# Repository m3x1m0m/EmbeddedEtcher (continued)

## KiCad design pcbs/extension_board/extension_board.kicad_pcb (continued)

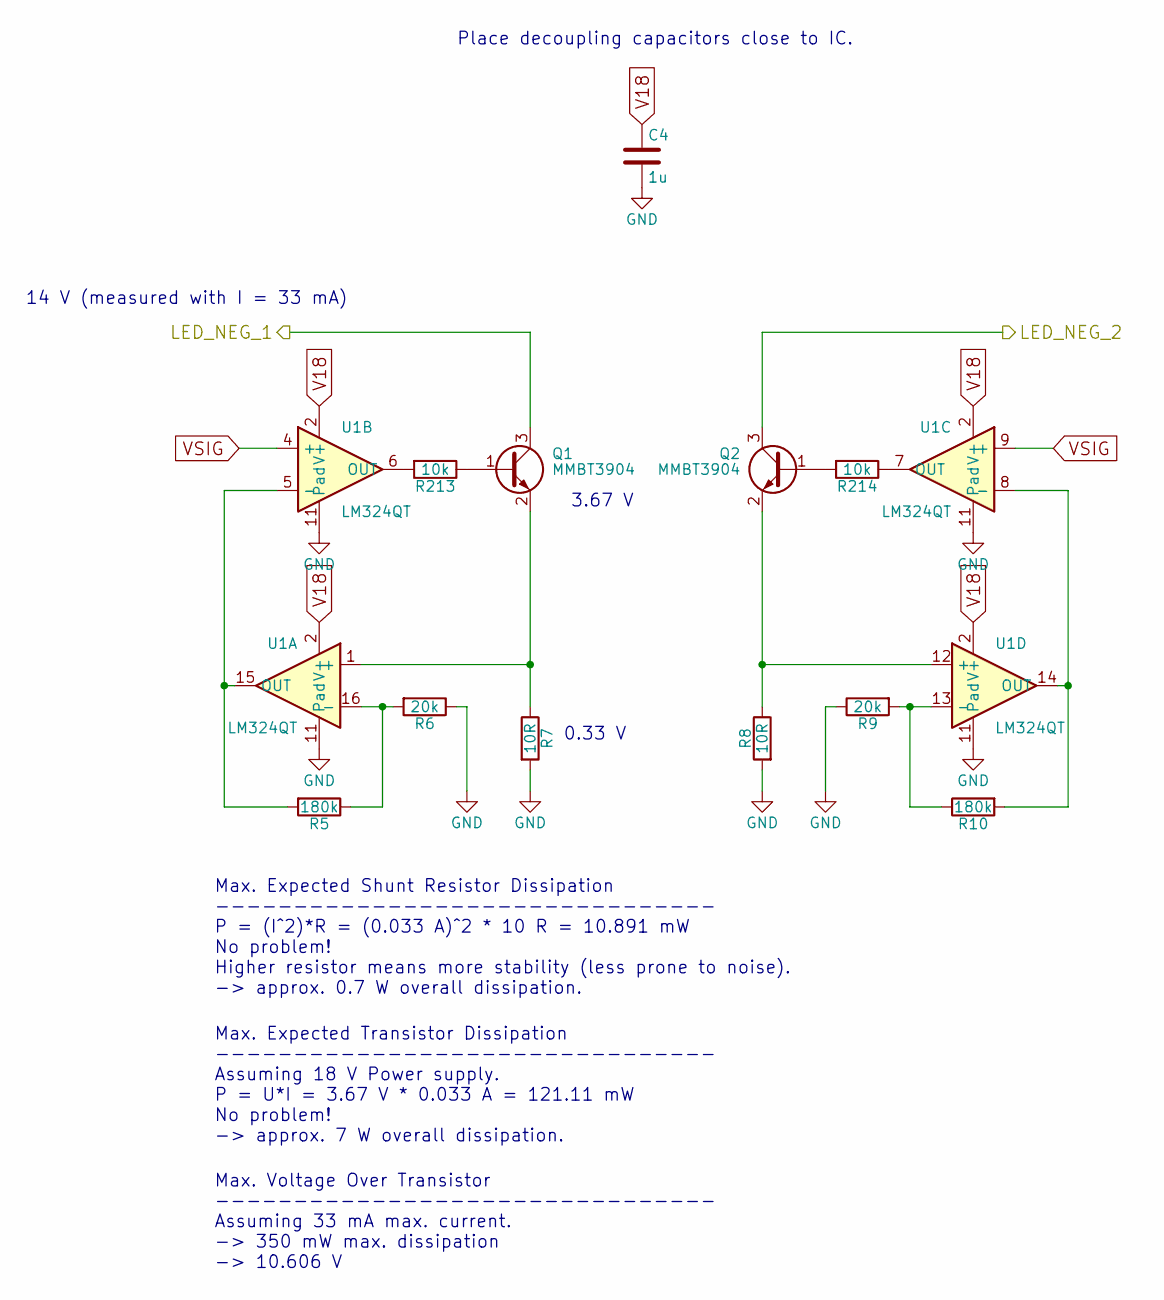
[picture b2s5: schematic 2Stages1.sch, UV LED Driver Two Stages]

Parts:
C4: 1u; R_0603; Digikey 399-3118-1-ND
Q1, Q2: MMBT3904; SOT-23; Digikey MMBT3904TPMSCT-ND
R5, R10: 180k; R_0603; Digikey 311-180KHRCT-ND
R6, R9: 20k; R_0603; Digikey 311-20.0KHRCT-ND
R7, R8: 10R; R_0603; Digikey 311-10.0HRCT-ND
R213, R214: 10k; R_0603; Digikey 311-10KGRCT-ND
U1: LM324QT; QFN-16-1EP_3x3mm_Pitch0.5mm; Digikey 497-12005-1-ND

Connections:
GND: C4.2, R6.1, R7.2, R8.2, R9.1, U1.11 (Pad), U1.17 (Pad); also elsewhere on the board
LED_N_01: Q1.3 (C); also elsewhere on the board
LED_N_02: Q2.3 (C); also elsewhere on the board
unnamed: Q1.1 (B), R213.1
unnamed: Q1.2 (E), R7.1, U1.1 (+)
unnamed: Q2.1 (B), R214.2
unnamed: Q2.2 (E), R8.1, U1.12 (+)
unnamed: R5.1, R6.2, U1.16 (-)
unnamed: R5.2, U1.5 (-), U1.15 (OUT)
unnamed: R9.2, R10.1, U1.13 (-)
unnamed: R10.2, U1.8 (-), U1.14 (OUT)
unnamed: R213.2, U1.6 (OUT)
unnamed: R214.1, U1.7 (OUT)
V18: C4.1, U1.2 (V+); also elsewhere on the board
VSIG: U1.4 (+), U1.9 (+); also elsewhere on the board

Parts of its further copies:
C8, C12, C16, C20, C24, C28, C32, C36, C40, C44, C48, C52, C56, C60, C64, C68, C72, C76, C80, C84, C88, C92, C96, C100, C104, C108, C112, C116, C120, C124, C128: 1u; R_0603; Digikey 399-3118-1-ND
Q3, Q4, Q5, Q6, Q7, Q8, Q9, Q10, Q11, Q12, Q13, Q14, Q15, Q16, Q17, Q18, Q19, Q20, Q21, Q22, Q23, Q24, Q25, Q26, Q27, Q28, Q29, Q30, Q31, Q32, Q33, Q34, Q35, Q36, Q37, Q38, Q39, Q40, Q41, Q42, Q43, Q44, Q45, Q46, Q47, Q48, Q49, Q50, Q51, Q52, Q53, Q54, Q55, Q56, Q57, Q58, Q59, Q60, Q61, Q62, Q63, Q64: MMBT3904; SOT-23; Digikey MMBT3904TPMSCT-ND
R11, R16, R17, R22, R23, R28, R29, R34, R35, R40, R41, R46, R47, R52, R53, R58, R59, R64, R65, R70, R71, R76, R77, R82, R83, R88, R89, R94, R95, R100, R101, R106, R107, R112, R113, R118, R119, R124, R125, R130, R131, R136, R137, R142, R143, R148, R149, R154, R155, R160, R161, R166, R167, R172, R173, R178, R179, R184, R185, R190, R191, R196: 180k; R_0603; Digikey 311-180KHRCT-ND
R12, R15, R18, R21, R24, R27, R30, R33, R36, R39, R42, R45, R48, R51, R54, R57, R60, R63, R66, R69, R72, R75, R78, R81, R84, R87, R90, R93, R96, R99, R102, R105, R108, R111, R114, R117, R120, R123, R126, R129, R132, R135, R138, R141, R144, R147, R150, R153, R156, R159, R162, R165, R168, R171, R174, R177, R180, R183, R186, R189, R192, R195: 20k; R_0603; Digikey 311-20.0KHRCT-ND
R13, R14, R19, R20, R25, R26, R31, R32, R37, R38, R43, R44, R49, R50, R55, R56, R61, R62, R67, R68, R73, R74, R79, R80, R85, R86, R91, R92, R97, R98, R103, R104, R109, R110, R115, R116, R121, R122, R127, R128, R133, R134, R139, R140, R145, R146, R151, R152, R157, R158, R163, R164, R169, R170, R175, R176, R181, R182, R187, R188, R193, R194: 10R; R_0603; Digikey 311-10.0HRCT-ND
R215, R216, R217, R218, R219, R220, R221, R222, R223, R224, R225, R226, R227, R228, R229, R230, R231, R232, R233, R234, R235, R236, R237, R238, R239, R240, R241, R242, R243, R244, R245, R246, R247, R248, R249, R250, R251, R252, R253, R254, R255, R256, R257, R258, R259, R260, R261, R262, R263, R264, R265, R266, R267, R268, R269, R270, R271, R272, R273, R274, R275, R276: 10k; R_0603; Digikey 311-10KGRCT-ND
U2, U3, U4, U5, U6, U7, U8, U9, U10, U11, U12, U13, U14, U15, U16, U17, U18, U19, U20, U21, U22, U23, U24, U25, U26, U27, U28, U29, U30, U31, U32: LM324QT; QFN-16-1EP_3x3mm_Pitch0.5mm; Digikey 497-12005-1-ND

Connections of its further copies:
GND: C8.2, C12.2, C16.2, C20.2, C24.2, C28.2, C32.2, C36.2, C40.2, C44.2, C48.2, C52.2, C56.2, C60.2, C64.2, C68.2, C72.2, C76.2, C80.2, C84.2, C88.2, C92.2, C96.2, C100.2, C104.2, C108.2, C112.2, C116.2, C120.2, C124.2, C128.2, R12.1, R13.2, R14.2, R15.1, R18.1, R19.2, R20.2, R21.1, R24.1, R25.2, R26.2, R27.1, R30.1, R31.2, R32.2, R33.1, R36.1, R37.2, R38.2, R39.1, R42.1, R43.2, R44.2, R45.1, R48.1, R49.2, R50.2, R51.1, R54.1, R55.2, R56.2, R57.1, R60.1, R61.2, R62.2, R63.1, R66.1, R67.2, R68.2, R69.1, R72.1, R73.2, R74.2, R75.1, R78.1, R79.2, R80.2, R81.1, R84.1, R85.2, R86.2, R87.1, R90.1, R91.2, R92.2, R93.1, R96.1, R97.2, R98.2, R99.1, R102.1, R103.2, R104.2, R105.1, R108.1, R109.2, R110.2, R111.1, R114.1, R115.2, R116.2, R117.1, R120.1, R121.2, R122.2, R123.1, R126.1, R127.2, R128.2, R129.1, R132.1, R133.2, R134.2, R135.1, R138.1, R139.2, R140.2, R141.1, R144.1, R145.2, R146.2, R147.1, R150.1, R151.2, R152.2, R153.1, R156.1, R157.2, R158.2, R159.1, R162.1, R163.2, R164.2, R165.1, R168.1, R169.2, R170.2, R171.1, R174.1, R175.2, R176.2, R177.1, R180.1, R181.2, R182.2, R183.1, R186.1, R187.2, R188.2, R189.1, R192.1, R193.2, R194.2, R195.1, U2.11 (Pad), U2.17 (Pad), U3.11 (Pad), U3.17 (Pad), U4.11 (Pad), U4.17 (Pad), U5.11 (Pad), U5.17 (Pad), U6.11 (Pad), U6.17 (Pad), U7.11 (Pad), U7.17 (Pad), U8.11 (Pad), U8.17 (Pad), U9.11 (Pad), U9.17 (Pad), U10.11 (Pad), U10.17 (Pad), U11.11 (Pad), U11.17 (Pad), U12.11 (Pad), U12.17 (Pad), U13.11 (Pad), U13.17 (Pad), U14.11 (Pad), U14.17 (Pad), U15.11 (Pad), U15.17 (Pad), U16.11 (Pad), U16.17 (Pad), U17.11 (Pad), U17.17 (Pad), U18.11 (Pad), U18.17 (Pad), U19.11 (Pad), U19.17 (Pad), U20.11 (Pad), U20.17 (Pad), U21.11 (Pad), U21.17 (Pad), U22.11 (Pad), U22.17 (Pad), U23.11 (Pad), U23.17 (Pad), U24.11 (Pad), U24.17 (Pad), U25.11 (Pad), U25.17 (Pad), U26.11 (Pad), U26.17 (Pad), U27.11 (Pad), U27.17 (Pad), U28.11 (Pad), U28.17 (Pad), U29.11 (Pad), U29.17 (Pad), U30.11 (Pad), U30.17 (Pad), U31.11 (Pad), U31.17 (Pad), U32.11 (Pad), U32.17 (Pad); also elsewhere on the board
LED_N_03: Q3.3 (C); also elsewhere on the board
LED_N_04: Q4.3 (C); also elsewhere on the board
LED_N_05: Q5.3 (C); also elsewhere on the board
LED_N_06: Q6.3 (C); also elsewhere on the board
LED_N_07: Q7.3 (C); also elsewhere on the board
LED_N_08: Q8.3 (C); also elsewhere on the board
LED_N_09: Q9.3 (C); also elsewhere on the board
LED_N_10: Q10.3 (C); also elsewhere on the board
LED_N_11: Q11.3 (C); also elsewhere on the board
LED_N_12: Q12.3 (C); also elsewhere on the board
LED_N_13: Q13.3 (C); also elsewhere on the board
LED_N_14: Q14.3 (C); also elsewhere on the board
LED_N_15: Q15.3 (C); also elsewhere on the board
LED_N_16: Q16.3 (C); also elsewhere on the board
LED_N_17: Q17.3 (C); also elsewhere on the board
LED_N_18: Q18.3 (C); also elsewhere on the board
LED_N_19: Q19.3 (C); also elsewhere on the board
LED_N_20: Q20.3 (C); also elsewhere on the board
LED_N_21: Q21.3 (C); also elsewhere on the board
LED_N_22: Q22.3 (C); also elsewhere on the board
LED_N_23: Q23.3 (C); also elsewhere on the board
LED_N_24: Q24.3 (C); also elsewhere on the board
LED_N_25: Q25.3 (C); also elsewhere on the board
LED_N_26: Q26.3 (C); also elsewhere on the board
LED_N_27: Q27.3 (C); also elsewhere on the board
LED_N_28: Q28.3 (C); also elsewhere on the board
LED_N_29: Q29.3 (C); also elsewhere on the board
LED_N_30: Q30.3 (C); also elsewhere on the board
LED_N_31: Q31.3 (C); also elsewhere on the board
LED_N_32: Q32.3 (C); also elsewhere on the board
LED_N_33: Q34.3 (C); also elsewhere on the board
LED_N_34: Q33.3 (C); also elsewhere on the board
LED_N_35: Q36.3 (C); also elsewhere on the board
LED_N_36: Q35.3 (C); also elsewhere on the board
LED_N_37: Q38.3 (C); also elsewhere on the board
LED_N_38: Q37.3 (C); also elsewhere on the board
LED_N_39: Q40.3 (C); also elsewhere on the board
LED_N_40: Q39.3 (C); also elsewhere on the board
LED_N_41: Q42.3 (C); also elsewhere on the board
LED_N_42: Q41.3 (C); also elsewhere on the board
LED_N_43: Q44.3 (C); also elsewhere on the board
LED_N_44: Q43.3 (C); also elsewhere on the board
LED_N_45: Q46.3 (C); also elsewhere on the board
LED_N_46: Q45.3 (C); also elsewhere on the board
LED_N_47: Q48.3 (C); also elsewhere on the board
LED_N_48: Q47.3 (C); also elsewhere on the board
LED_N_49: Q50.3 (C); also elsewhere on the board
LED_N_50: Q49.3 (C); also elsewhere on the board
LED_N_51: Q52.3 (C); also elsewhere on the board
LED_N_52: Q51.3 (C); also elsewhere on the board
LED_N_53: Q54.3 (C); also elsewhere on the board
LED_N_54: Q53.3 (C); also elsewhere on the board
LED_N_55: Q56.3 (C); also elsewhere on the board
LED_N_56: Q55.3 (C); also elsewhere on the board
LED_N_57: Q58.3 (C); also elsewhere on the board
LED_N_58: Q57.3 (C); also elsewhere on the board
LED_N_59: Q60.3 (C); also elsewhere on the board
LED_N_60: Q59.3 (C); also elsewhere on the board
LED_N_61: Q62.3 (C); also elsewhere on the board
LED_N_62: Q61.3 (C); also elsewhere on the board
LED_N_63: Q64.3 (C); also elsewhere on the board
LED_N_64: Q63.3 (C); also elsewhere on the board
unnamed: Q3.1 (B), R215.1
unnamed: Q3.2 (E), R13.1, U2.1 (+)
unnamed: Q4.1 (B), R216.2
unnamed: Q4.2 (E), R14.1, U2.12 (+)
unnamed: Q5.1 (B), R217.1
unnamed: Q5.2 (E), R19.1, U3.1 (+)
unnamed: Q6.1 (B), R218.2
unnamed: Q6.2 (E), R20.1, U3.12 (+)
unnamed: Q7.1 (B), R219.1
unnamed: Q7.2 (E), R25.1, U4.1 (+)
unnamed: Q8.1 (B), R220.2
unnamed: Q8.2 (E), R26.1, U4.12 (+)
unnamed: Q9.1 (B), R221.1
unnamed: Q9.2 (E), R31.1, U5.1 (+)
unnamed: Q10.1 (B), R222.2
unnamed: Q10.2 (E), R32.1, U5.12 (+)
unnamed: Q11.1 (B), R223.1
unnamed: Q11.2 (E), R37.1, U6.1 (+)
unnamed: Q12.1 (B), R224.2
unnamed: Q12.2 (E), R38.1, U6.12 (+)
unnamed: Q13.1 (B), R225.1
unnamed: Q13.2 (E), R43.1, U7.1 (+)
unnamed: Q14.1 (B), R226.2
unnamed: Q14.2 (E), R44.1, U7.12 (+)
unnamed: Q15.1 (B), R227.1
unnamed: Q15.2 (E), R49.1, U8.1 (+)
unnamed: Q16.1 (B), R228.2
unnamed: Q16.2 (E), R50.1, U8.12 (+)
unnamed: Q17.1 (B), R229.1
unnamed: Q17.2 (E), R55.1, U9.1 (+)
unnamed: Q18.1 (B), R230.2
unnamed: Q18.2 (E), R56.1, U9.12 (+)
unnamed: Q19.1 (B), R231.1
unnamed: Q19.2 (E), R61.1, U10.1 (+)
unnamed: Q20.1 (B), R232.2
unnamed: Q20.2 (E), R62.1, U10.12 (+)
unnamed: Q21.1 (B), R233.1
unnamed: Q21.2 (E), R67.1, U11.1 (+)
unnamed: Q22.1 (B), R234.2
unnamed: Q22.2 (E), R68.1, U11.12 (+)
unnamed: Q23.1 (B), R235.1
unnamed: Q23.2 (E), R73.1, U12.1 (+)
unnamed: Q24.1 (B), R236.2
unnamed: Q24.2 (E), R74.1, U12.12 (+)
unnamed: Q25.1 (B), R237.1
unnamed: Q25.2 (E), R79.1, U13.1 (+)
unnamed: Q26.1 (B), R238.2
unnamed: Q26.2 (E), R80.1, U13.12 (+)
unnamed: Q27.1 (B), R239.1
unnamed: Q27.2 (E), R85.1, U14.1 (+)
unnamed: Q28.1 (B), R240.2
unnamed: Q28.2 (E), R86.1, U14.12 (+)
unnamed: Q29.1 (B), R241.1
unnamed: Q29.2 (E), R91.1, U15.1 (+)
unnamed: Q30.1 (B), R242.2
unnamed: Q30.2 (E), R92.1, U15.12 (+)
unnamed: Q31.1 (B), R243.1
unnamed: Q31.2 (E), R97.1, U16.1 (+)
unnamed: Q32.1 (B), R244.2
unnamed: Q32.2 (E), R98.1, U16.12 (+)
unnamed: Q33.1 (B), R275.1
unnamed: Q33.2 (E), R193.1, U17.1 (+)
unnamed: Q34.1 (B), R276.2
unnamed: Q34.2 (E), R194.1, U17.12 (+)
unnamed: Q35.1 (B), R273.1
unnamed: Q35.2 (E), R187.1, U18.1 (+)
unnamed: Q36.1 (B), R274.2
unnamed: Q36.2 (E), R188.1, U18.12 (+)
unnamed: Q37.1 (B), R271.1
unnamed: Q37.2 (E), R181.1, U19.1 (+)
unnamed: Q38.1 (B), R272.2
unnamed: Q38.2 (E), R182.1, U19.12 (+)
unnamed: Q39.1 (B), R269.1
unnamed: Q39.2 (E), R175.1, U20.1 (+)
unnamed: Q40.1 (B), R270.2
unnamed: Q40.2 (E), R176.1, U20.12 (+)
unnamed: Q41.1 (B), R267.1
unnamed: Q41.2 (E), R169.1, U21.1 (+)
unnamed: Q42.1 (B), R268.2
unnamed: Q42.2 (E), R170.1, U21.12 (+)
unnamed: Q43.1 (B), R265.1
unnamed: Q43.2 (E), R163.1, U22.1 (+)
unnamed: Q44.1 (B), R266.2
unnamed: Q44.2 (E), R164.1, U22.12 (+)
unnamed: Q45.1 (B), R263.1
unnamed: Q45.2 (E), R157.1, U23.1 (+)
unnamed: Q46.1 (B), R264.2
unnamed: Q46.2 (E), R158.1, U23.12 (+)
unnamed: Q47.1 (B), R261.1
unnamed: Q47.2 (E), R151.1, U24.1 (+)
unnamed: Q48.1 (B), R262.2
unnamed: Q48.2 (E), R152.1, U24.12 (+)
unnamed: Q49.1 (B), R259.1
unnamed: Q49.2 (E), R145.1, U25.1 (+)
unnamed: Q50.1 (B), R260.2
unnamed: Q50.2 (E), R146.1, U25.12 (+)
unnamed: Q51.1 (B), R257.1
unnamed: Q51.2 (E), R139.1, U26.1 (+)
unnamed: Q52.1 (B), R258.2
unnamed: Q52.2 (E), R140.1, U26.12 (+)
unnamed: Q53.1 (B), R255.1
unnamed: Q53.2 (E), R133.1, U27.1 (+)
unnamed: Q54.1 (B), R256.2
unnamed: Q54.2 (E), R134.1, U27.12 (+)
unnamed: Q55.1 (B), R253.1
unnamed: Q55.2 (E), R127.1, U28.1 (+)
unnamed: Q56.1 (B), R254.2
unnamed: Q56.2 (E), R128.1, U28.12 (+)
unnamed: Q57.1 (B), R251.1
unnamed: Q57.2 (E), R121.1, U29.1 (+)
unnamed: Q58.1 (B), R252.2
unnamed: Q58.2 (E), R122.1, U29.12 (+)
unnamed: Q59.1 (B), R249.1
unnamed: Q59.2 (E), R115.1, U30.1 (+)
unnamed: Q60.1 (B), R250.2
unnamed: Q60.2 (E), R116.1, U30.12 (+)
unnamed: Q61.1 (B), R247.1
unnamed: Q61.2 (E), R109.1, U31.1 (+)
unnamed: Q62.1 (B), R248.2
unnamed: Q62.2 (E), R110.1, U31.12 (+)
unnamed: Q63.1 (B), R245.1
unnamed: Q63.2 (E), R103.1, U32.1 (+)
unnamed: Q64.1 (B), R246.2
unnamed: Q64.2 (E), R104.1, U32.12 (+)
unnamed: R11.1, R12.2, U2.16 (-)
unnamed: R11.2, U2.5 (-), U2.15 (OUT)
unnamed: R15.2, R16.1, U2.13 (-)
unnamed: R16.2, U2.8 (-), U2.14 (OUT)
unnamed: R17.1, R18.2, U3.16 (-)
unnamed: R17.2, U3.5 (-), U3.15 (OUT)
unnamed: R21.2, R22.1, U3.13 (-)
unnamed: R22.2, U3.8 (-), U3.14 (OUT)
unnamed: R23.1, R24.2, U4.16 (-)
unnamed: R23.2, U4.5 (-), U4.15 (OUT)
unnamed: R27.2, R28.1, U4.13 (-)
unnamed: R28.2, U4.8 (-), U4.14 (OUT)
unnamed: R29.1, R30.2, U5.16 (-)
unnamed: R29.2, U5.5 (-), U5.15 (OUT)
unnamed: R33.2, R34.1, U5.13 (-)
unnamed: R34.2, U5.8 (-), U5.14 (OUT)
unnamed: R35.1, R36.2, U6.16 (-)
unnamed: R35.2, U6.5 (-), U6.15 (OUT)
unnamed: R39.2, R40.1, U6.13 (-)
unnamed: R40.2, U6.8 (-), U6.14 (OUT)
unnamed: R41.1, R42.2, U7.16 (-)
unnamed: R41.2, U7.5 (-), U7.15 (OUT)
unnamed: R45.2, R46.1, U7.13 (-)
unnamed: R46.2, U7.8 (-), U7.14 (OUT)
unnamed: R47.1, R48.2, U8.16 (-)
unnamed: R47.2, U8.5 (-), U8.15 (OUT)
unnamed: R51.2, R52.1, U8.13 (-)
unnamed: R52.2, U8.8 (-), U8.14 (OUT)
unnamed: R53.1, R54.2, U9.16 (-)
unnamed: R53.2, U9.5 (-), U9.15 (OUT)
unnamed: R57.2, R58.1, U9.13 (-)
unnamed: R58.2, U9.8 (-), U9.14 (OUT)
unnamed: R59.1, R60.2, U10.16 (-)
unnamed: R59.2, U10.5 (-), U10.15 (OUT)
unnamed: R63.2, R64.1, U10.13 (-)
unnamed: R64.2, U10.8 (-), U10.14 (OUT)
unnamed: R65.1, R66.2, U11.16 (-)
unnamed: R65.2, U11.5 (-), U11.15 (OUT)
unnamed: R69.2, R70.1, U11.13 (-)
unnamed: R70.2, U11.8 (-), U11.14 (OUT)
unnamed: R71.1, R72.2, U12.16 (-)
unnamed: R71.2, U12.5 (-), U12.15 (OUT)
unnamed: R75.2, R76.1, U12.13 (-)
unnamed: R76.2, U12.8 (-), U12.14 (OUT)
unnamed: R77.1, R78.2, U13.16 (-)
unnamed: R77.2, U13.5 (-), U13.15 (OUT)
unnamed: R81.2, R82.1, U13.13 (-)
unnamed: R82.2, U13.8 (-), U13.14 (OUT)
unnamed: R83.1, R84.2, U14.16 (-)
unnamed: R83.2, U14.5 (-), U14.15 (OUT)
unnamed: R87.2, R88.1, U14.13 (-)
unnamed: R88.2, U14.8 (-), U14.14 (OUT)
unnamed: R89.1, R90.2, U15.16 (-)
unnamed: R89.2, U15.5 (-), U15.15 (OUT)
unnamed: R93.2, R94.1, U15.13 (-)
unnamed: R94.2, U15.8 (-), U15.14 (OUT)
unnamed: R95.1, R96.2, U16.16 (-)
unnamed: R95.2, U16.5 (-), U16.15 (OUT)
unnamed: R99.2, R100.1, U16.13 (-)
unnamed: R100.2, U16.8 (-), U16.14 (OUT)
unnamed: R101.1, R102.2, U32.16 (-)
unnamed: R101.2, U32.5 (-), U32.15 (OUT)
unnamed: R105.2, R106.1, U32.13 (-)
unnamed: R106.2, U32.8 (-), U32.14 (OUT)
unnamed: R107.1, R108.2, U31.16 (-)
unnamed: R107.2, U31.5 (-), U31.15 (OUT)
unnamed: R111.2, R112.1, U31.13 (-)
unnamed: R112.2, U31.8 (-), U31.14 (OUT)
unnamed: R113.1, R114.2, U30.16 (-)
unnamed: R113.2, U30.5 (-), U30.15 (OUT)
unnamed: R117.2, R118.1, U30.13 (-)
unnamed: R118.2, U30.8 (-), U30.14 (OUT)
unnamed: R119.1, R120.2, U29.16 (-)
unnamed: R119.2, U29.5 (-), U29.15 (OUT)
unnamed: R123.2, R124.1, U29.13 (-)
unnamed: R124.2, U29.8 (-), U29.14 (OUT)
unnamed: R125.1, R126.2, U28.16 (-)
unnamed: R125.2, U28.5 (-), U28.15 (OUT)
unnamed: R129.2, R130.1, U28.13 (-)
unnamed: R130.2, U28.8 (-), U28.14 (OUT)
unnamed: R131.1, R132.2, U27.16 (-)
unnamed: R131.2, U27.5 (-), U27.15 (OUT)
unnamed: R135.2, R136.1, U27.13 (-)
unnamed: R136.2, U27.8 (-), U27.14 (OUT)
unnamed: R137.1, R138.2, U26.16 (-)
unnamed: R137.2, U26.5 (-), U26.15 (OUT)
unnamed: R141.2, R142.1, U26.13 (-)
unnamed: R142.2, U26.8 (-), U26.14 (OUT)
unnamed: R143.1, R144.2, U25.16 (-)
unnamed: R143.2, U25.5 (-), U25.15 (OUT)
unnamed: R147.2, R148.1, U25.13 (-)
unnamed: R148.2, U25.8 (-), U25.14 (OUT)
unnamed: R149.1, R150.2, U24.16 (-)
unnamed: R149.2, U24.5 (-), U24.15 (OUT)
unnamed: R153.2, R154.1, U24.13 (-)
unnamed: R154.2, U24.8 (-), U24.14 (OUT)
unnamed: R155.1, R156.2, U23.16 (-)
unnamed: R155.2, U23.5 (-), U23.15 (OUT)
unnamed: R159.2, R160.1, U23.13 (-)
unnamed: R160.2, U23.8 (-), U23.14 (OUT)
unnamed: R161.1, R162.2, U22.16 (-)
unnamed: R161.2, U22.5 (-), U22.15 (OUT)
unnamed: R165.2, R166.1, U22.13 (-)
unnamed: R166.2, U22.8 (-), U22.14 (OUT)
unnamed: R167.1, R168.2, U21.16 (-)
unnamed: R167.2, U21.5 (-), U21.15 (OUT)
unnamed: R171.2, R172.1, U21.13 (-)
unnamed: R172.2, U21.8 (-), U21.14 (OUT)
unnamed: R173.1, R174.2, U20.16 (-)
unnamed: R173.2, U20.5 (-), U20.15 (OUT)
unnamed: R177.2, R178.1, U20.13 (-)
unnamed: R178.2, U20.8 (-), U20.14 (OUT)
unnamed: R179.1, R180.2, U19.16 (-)
unnamed: R179.2, U19.5 (-), U19.15 (OUT)
unnamed: R183.2, R184.1, U19.13 (-)
unnamed: R184.2, U19.8 (-), U19.14 (OUT)
unnamed: R185.1, R186.2, U18.16 (-)
unnamed: R185.2, U18.5 (-), U18.15 (OUT)
unnamed: R189.2, R190.1, U18.13 (-)
unnamed: R190.2, U18.8 (-), U18.14 (OUT)
unnamed: R191.1, R192.2, U17.16 (-)
unnamed: R191.2, U17.5 (-), U17.15 (OUT)
unnamed: R195.2, R196.1, U17.13 (-)
unnamed: R196.2, U17.8 (-), U17.14 (OUT)
unnamed: R215.2, U2.6 (OUT)
unnamed: R216.1, U2.7 (OUT)
unnamed: R217.2, U3.6 (OUT)
unnamed: R218.1, U3.7 (OUT)
unnamed: R219.2, U4.6 (OUT)
unnamed: R220.1, U4.7 (OUT)
unnamed: R221.2, U5.6 (OUT)
unnamed: R222.1, U5.7 (OUT)
unnamed: R223.2, U6.6 (OUT)
unnamed: R224.1, U6.7 (OUT)
unnamed: R225.2, U7.6 (OUT)
unnamed: R226.1, U7.7 (OUT)
unnamed: R227.2, U8.6 (OUT)
unnamed: R228.1, U8.7 (OUT)
unnamed: R229.2, U9.6 (OUT)
unnamed: R230.1, U9.7 (OUT)
unnamed: R231.2, U10.6 (OUT)
unnamed: R232.1, U10.7 (OUT)
unnamed: R233.2, U11.6 (OUT)
unnamed: R234.1, U11.7 (OUT)
unnamed: R235.2, U12.6 (OUT)
unnamed: R236.1, U12.7 (OUT)
unnamed: R237.2, U13.6 (OUT)
unnamed: R238.1, U13.7 (OUT)
unnamed: R239.2, U14.6 (OUT)
unnamed: R240.1, U14.7 (OUT)
unnamed: R241.2, U15.6 (OUT)
unnamed: R242.1, U15.7 (OUT)
unnamed: R243.2, U16.6 (OUT)
unnamed: R244.1, U16.7 (OUT)
unnamed: R245.2, U32.6 (OUT)
unnamed: R246.1, U32.7 (OUT)
unnamed: R247.2, U31.6 (OUT)
unnamed: R248.1, U31.7 (OUT)
unnamed: R249.2, U30.6 (OUT)
unnamed: R250.1, U30.7 (OUT)
unnamed: R251.2, U29.6 (OUT)
unnamed: R252.1, U29.7 (OUT)
unnamed: R253.2, U28.6 (OUT)
unnamed: R254.1, U28.7 (OUT)
unnamed: R255.2, U27.6 (OUT)
unnamed: R256.1, U27.7 (OUT)
unnamed: R257.2, U26.6 (OUT)
unnamed: R258.1, U26.7 (OUT)
unnamed: R259.2, U25.6 (OUT)
unnamed: R260.1, U25.7 (OUT)
unnamed: R261.2, U24.6 (OUT)
unnamed: R262.1, U24.7 (OUT)
unnamed: R263.2, U23.6 (OUT)
unnamed: R264.1, U23.7 (OUT)
unnamed: R265.2, U22.6 (OUT)
unnamed: R266.1, U22.7 (OUT)
unnamed: R267.2, U21.6 (OUT)
unnamed: R268.1, U21.7 (OUT)
unnamed: R269.2, U20.6 (OUT)
unnamed: R270.1, U20.7 (OUT)
unnamed: R271.2, U19.6 (OUT)
unnamed: R272.1, U19.7 (OUT)
unnamed: R273.2, U18.6 (OUT)
unnamed: R274.1, U18.7 (OUT)
unnamed: R275.2, U17.6 (OUT)
unnamed: R276.1, U17.7 (OUT)
V18: C8.1, C12.1, C16.1, C20.1, C24.1, C28.1, C32.1, C36.1, C40.1, C44.1, C48.1, C52.1, C56.1, C60.1, C64.1, C68.1, C72.1, C76.1, C80.1, C84.1, C88.1, C92.1, C96.1, C100.1, C104.1, C108.1, C112.1, C116.1, C120.1, C124.1, C128.1, U2.2 (V+), U3.2 (V+), U4.2 (V+), U5.2 (V+), U6.2 (V+), U7.2 (V+), U8.2 (V+), U9.2 (V+), U10.2 (V+), U11.2 (V+), U12.2 (V+), U13.2 (V+), U14.2 (V+), U15.2 (V+), U16.2 (V+), U17.2 (V+), U18.2 (V+), U19.2 (V+), U20.2 (V+), U21.2 (V+), U22.2 (V+), U23.2 (V+), U24.2 (V+), U25.2 (V+), U26.2 (V+), U27.2 (V+), U28.2 (V+), U29.2 (V+), U30.2 (V+), U31.2 (V+), U32.2 (V+); also elsewhere on the board
VSIG: U2.4 (+), U2.9 (+), U3.4 (+), U3.9 (+), U4.4 (+), U4.9 (+), U5.4 (+), U5.9 (+), U6.4 (+), U6.9 (+), U7.4 (+), U7.9 (+), U8.4 (+), U8.9 (+), U9.4 (+), U9.9 (+), U10.4 (+), U10.9 (+), U11.4 (+), U11.9 (+), U12.4 (+), U12.9 (+), U13.4 (+), U13.9 (+), U14.4 (+), U14.9 (+), U15.4 (+), U15.9 (+), U16.4 (+), U16.9 (+), U17.4 (+), U17.9 (+), U18.4 (+), U18.9 (+), U19.4 (+), U19.9 (+), U20.4 (+), U20.9 (+), U21.4 (+), U21.9 (+), U22.4 (+), U22.9 (+), U23.4 (+), U23.9 (+), U24.4 (+), U24.9 (+), U25.4 (+), U25.9 (+), U26.4 (+), U26.9 (+), U27.4 (+), U27.9 (+), U28.4 (+), U28.9 (+), U29.4 (+), U29.9 (+), U30.4 (+), U30.9 (+), U31.4 (+), U31.9 (+), U32.4 (+), U32.9 (+); also elsewhere on the board

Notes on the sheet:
Place decoupling capacitors close to IC.
Max. Expected Shunt Resistor Dissipation -------------------------------- P = (I^2)*R = (0.033 A)^2 * 10 R = 10.891 mW No problem! Higher resistor means more stability (less prone to noise). -> approx. 0.7 W overall dissipation.
14 V (measured with I = 33 mA)
0.33 V
3.67 V
Max. Expected Transistor Dissipation -------------------------------- Assuming 18 V Power supply. P = U*I = 3.67 V * 0.033 A = 121.11 mW No problem! -> approx. 7 W overall dissipation.
Max. Voltage Over Transistor -------------------------------- Assuming 33 mA max. current. -> 350 mW max. dissipation -> 10.606 V

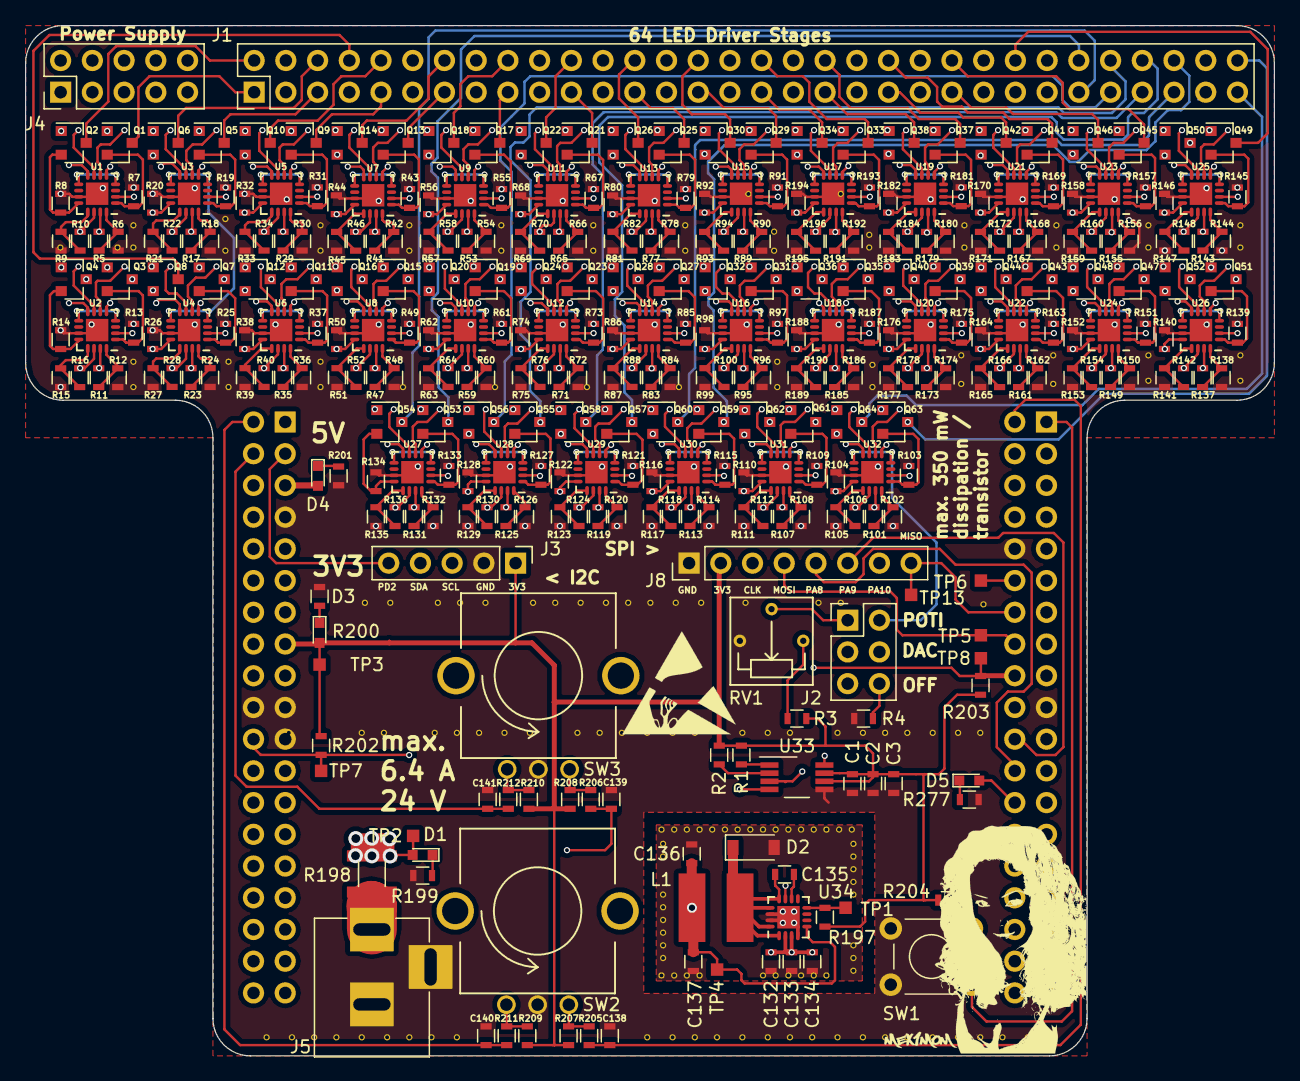
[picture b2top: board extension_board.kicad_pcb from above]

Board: 4 copper layers, 100.0 x 82.5 mm, 447 parts (0 on the bottom side), 421 nets.

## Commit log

2017-06-18 Initial commit.
2017-06-18 Finished CAD work.
2017-06-18 Cleaning.
2017-06-18 Modified README.md
2017-06-18 Added one .gitignore for KiCAD and developed a protection circuit for the LED driver.
2017-06-19 Finished third version of LED driver.
2017-11-12 Started layouting.
2017-11-13 LED driver part done.
2017-11-14 Only UI is left for schematics.
2017-11-14 Almost done with schematics. SPI OLED is missing.
2017-11-16 No DRC errors anymore in schematics.
2017-11-19 All components placed.
2017-11-21 Some progress layouting the beast today.
2017-11-22 Started eliminating DRC errors.
2017-11-27 Finished layouting the extension board.
2017-11-27 Added SPI_MISO to SPI interface.
2017-11-28 Added an adapter board (2 layers).
2017-11-30 Changed transistor array of driver for SOT-23 discrete transistor (more dissipation allowed).
2017-11-30 Added LaTeX .gitignore.
2017-12-05 Produced Gerber files for both boards. Ready for production.
2017-12-06 Updated current rating of extension board.
2017-12-07 Non-blocking UART driver seems to do its job, also the queues seem to work. No semaphores implemented yet.
2017-12-08 osPrintf works with signed and unsigned integers.
2017-12-11 Added more OS files to be tracked. Port them now to the STM32.
2017-12-12 OS up and running. Not perfect yet, though.
2018-02-11 Some updates.
2018-02-18 Updated README. Added report.
2018-02-18 Fixed problem with report.
2018-02-18 Updated README.
